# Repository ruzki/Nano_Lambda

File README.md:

# Nano_Lambda
Wideband Lambda shield for Arduino Nano <br />
License <br />

<br />
KiCad Project about a Wideband Lambda shield for the Arduino Nano <br />
Analog output signal can be generate via 2x MCP4725 or an PWM driven Op-Amp <br />

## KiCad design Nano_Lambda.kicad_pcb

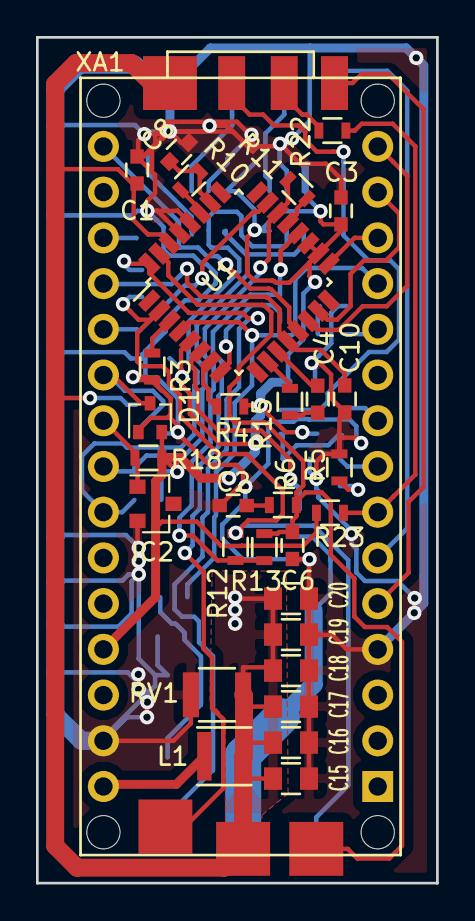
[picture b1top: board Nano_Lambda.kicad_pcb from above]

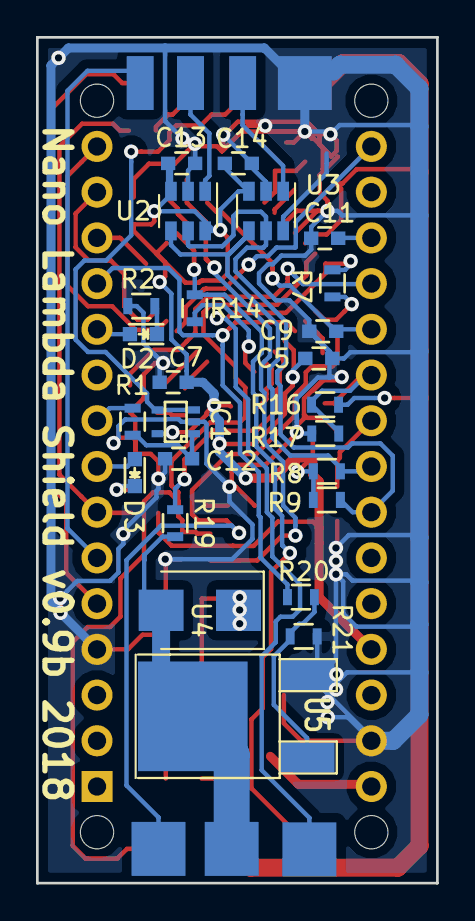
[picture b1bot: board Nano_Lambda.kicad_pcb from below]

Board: 2 copper layers, 22.2 x 47.0 mm, 70 parts (32 on the bottom side), 47 nets.

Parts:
C1, C3, C4, C5, C7, C8, C11, C12, C13, C14: 100n; C_0603
C2: 2.2n; C_0603
C6: C; C_0603
C9, C10: 33n; C_0603
C15, C16, C17, C18, C20: 22µF 25V; C_0805
C19: 6x 22µF 25V; C_0805
D1: BAT54S; SOT-323
D2: Blue; LED-0603
D3: red; LED-0603
IC1: LMV321?M5; SC-70-5
IC2: LM4041DBZ; SOT-23
J1: +12_IN; 3x3_PAD
J2: GND; 3x3_PAD
J3: +12V_NL; 3x3_PAD
J4: IP; 3x3_PAD
J5: UN; 3x3_PAD
J6: NL_HEATER; 3x3_PAD
J7: IA; 3x3_PAD
J8: VM; 3x3_PAD
J9: PD2; 1.5x3_PAD
J10: PD3; 1.5x3_PAD
J11: GP3; 1.5x3_PAD
J12: DAC1; 1.5x3_PAD
J13: DAC2; 1.5x3_PAD
J14: Out1; 1.5x3_PAD
L1: 22µH; Inductor_Taiyo-Yuden_MD-3030
R1, R3, R4, R8, R9, R17: 10k; R_0603
R2, R5: 1k; R_0603
R6: R; R_0603
R7: 61.9R; R_0603
R10, R13, R21, R23: 100k; R_0603
R11, R20, R22: 4.7k; R_0603
R12: 470k; R_0603
R14: 300R / 1%; R_0603
R15: 31.6k / 1%; R_0603
R16, R18: 39k; R_0603
R19: 6.8k; R_0603
RV1: Varistor; R_1210
U1: CJ125_32; LQFP-32_7x7mm_Pitch0.8mm
U2, U3: MCP4725; SOT-23-6
U4: MURS120; SMB_Standard
U5: IRLZ44; DPAKGDS
XA1: Arduino_Nano_Socket

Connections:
+5V: C3.1, C5.1, C7.2, C13.2, C14.2, D1.2, IC1.5, R4.2, R8.2, R9.2, R18.2, R23.1, U1.5, U1.18, U1.19, U2.3, U2.6, U3.3, XA1.5V
/+12V_NL: C1.1, C15.2, C16.2, C17.2, C18.2, C19.2, C20.2, J1.1, J3.1, L1.2, R16.2, RV1.1, U1.30, U4.1
/BRV: D1.3, R16.1, R17.2, XA1.A2
/CM: C4.2, R15.1
/DAC1: J12.1, U3.1
/DAC2: J13.1, U2.1
/DIAHD: R19.2, U1.6
/DIAHG: R20.2, U1.4, XA1.D9
/GP3: J11.1, R22.1
/IA: J7.1, R7.2, R12.1, U1.2
/IP: J4.1, R7.1, U1.32
/LED_1: D2.2, XA1.D8
/LED_2: D3.2, XA1.D5
/LS_MISO: U1.14, XA1.D12
/LS_MOSI: U1.15, XA1.D11
/LS_SCK: U1.13, XA1.D13
/LS_SS: U1.17, XA1.D10
/NL_HEATER: J6.1, R19.1, U4.2, U5.D
/Out1: IC1.3, IC1.4, J14.1
/PD2: J9.1, XA1.D2
/PD3: J10.1, XA1.D3
/RM: R15.2, U1.10
/RS: R14.1, U1.8
/SCL: R9.1, U2.5, U3.5, XA1.A5
/SDA: R8.1, U2.4, U3.4, XA1.A4
/UA: C9.1, U1.23, XA1.A1
/UN: C6.1, J5.1, R6.1, R13.1, U1.31
/UR: C10.1, U1.12, XA1.A0
/VM: J8.1, R14.2, U1.20
/V_REF: IC2.1, R18.1, XA1.A3
/WBL: R1.2, XA1.D6
GND: C1.2, C2.2, C3.2, C5.2, C6.2, C7.1, C8.1, C9.2, C10.2, C11.2, C12.1, C13.1, C14.1, C15.1, C16.1, C17.1, C18.1, C19.1, C20.1, D1.1, IC1.2, IC2.2, J2.1, R2.1, R3.2, R5.1, R17.1, R21.1, RV1.2, U1.28, U1.29, U2.2, U3.2, U3.6, U5.S, XA1.GND1, XA1.GND2
unnamed: C2.1, R6.2
unnamed: C4.1, U1.11
unnamed: C8.2, R10.1, U1.26
unnamed: C11.1, XA1.AREF
unnamed: C12.2, IC1.1, R1.1
unnamed: D2.1, R2.2
unnamed: D3.1, R5.2
unnamed: L1.1, XA1.VIN
unnamed: R3.1, U1.3
unnamed: R4.1, U1.7
unnamed: R10.2, U1.27
unnamed: R11.1, R12.2, R13.2, U1.22
unnamed: R11.2, U1.21
unnamed: R20.1, R21.2, U5.G
unnamed: R22.2, R23.2, XA1.D4

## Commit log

2018-09-03 Initial commit
    Version 0.9
2018-09-03 Updated Readme.md
    License Information added
2018-09-13 Change to Version 0.9b
    Changed wrong CJ125 Footprint to Footprint with 0.8mm pitch.
2018-09-15 Minor changes and new gerber files
2018-09-16 Fabrication version 0.9b
    Fabrication version 0.9b
2018-09-29 Diode u4 wrong direction
    Swapped pin numbers on Diode MURS120 symbol in schematic. Changed pin 1
    to 2 and 2 to 1

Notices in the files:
README.md:
License: CC BY-NC 4.0
